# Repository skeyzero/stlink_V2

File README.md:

# STLink V2  Designed with KiCAD

## 说明  
本工程为Kicad工程，里面提供改硬件对应固件。使用说明请往下看。    

## 使用说明:
1.通过别的下载器将固件烧录进去。烧录成功后插入电脑能检测到stlink设备。   
2.打开stm32 ST-Link Utility.选择 ST-Link -> Firmware update 刷路最新固件。(这里通过usb更新固件,并非通过别的下载器更新)。    
3.完毕。 

## 原理图

## 效果图   

## 友情广告
PCB设计推荐软件Kicad，功能强大，开源免费,免除律师函警告。       
QQ群:924407324

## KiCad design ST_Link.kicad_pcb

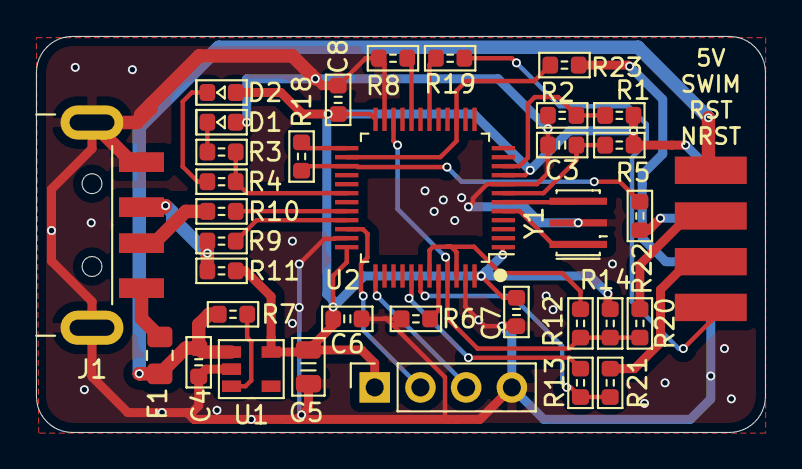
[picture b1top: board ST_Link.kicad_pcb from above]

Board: 2 copper layers, 40.5 x 22.0 mm, 36 parts (1 on the bottom side), 33 nets.

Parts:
C3: 22pF; 0603_C
C4: 1uF; 0603_C
C5: 10uF; 0805_C
C6, C7, C8: 100nF; 0603_C
D1: LED_B; 0603_LED
D2: LED_R; 0603_LED
F1: 0.5A; Fuse_0805_2012Metric_Pad1.15x1.40mm_HandSolder
J1: USB_A; USB_A_CNCTech_1001-011-01101_Horizontal
J2: Debug; PinSocket_1x04_P2.54mm_Vertical
J4: SWIM; cn_smt_2.54
J5: SWD; cn_smt_2.54
R1, R2: 4.7k; 0603_R
R3, R4, R11: 1k; 0603_R
R5, R6, R7, R8: 10k; 0603_R
R9, R10: 22R; 0603_R
R12, R13: 220R; 0603_R
R14: 680R; 0603_R
R18: 100R; 0603_R
R19, R20, R21, R22, R23: 20R; 0603_R
U1: ME6211C; SOT-23-5
U2: STM32F103_LQFP48; LQFP-48_7x7mm_P0.5mm
Y1: Crystal_CSTCE8M00; Resonator_SMD_muRata_CSTxExxV-3Pin_3.0x1.1mm_HandSoldering

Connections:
+3V3: C5.1, C6.1, C7.1, C8.1, D2.1, J2.1, J5.1, R1.1, R5.1, R11.1, R14.2, U1.5, U2.1, U2.9, U2.24, U2.36, U2.48
+5V: C4.1, F1.1, J4.1, R7.1, U1.1
/BOOT0: R6.1, U2.44
/BOOT1: R8.1, U2.20
/ISP_SWCLK: J2.3, U2.37
/ISP_SWDIO: J2.2, U2.34
/JTCK: R23.2, U2.15, U2.26
/JTMS: R18.1, R22.2, U2.27
/LED: R3.1, R4.1, U2.30
/NRST: R19.2, U2.18
/OSC_IN: U2.5, Y1.1
/OSC_OUT: U2.6, Y1.3
/PA0: R1.2, R2.1, U2.10
/RST: C3.1, R5.2, U2.7
/SWDIO_IN: R18.2, U2.25
/SWIM: R12.1, R14.1, R20.2, U2.22, U2.45
/SWIM_IN: R12.2, U2.43, U2.46
/SWIM_RST: R13.1, R21.2, U2.42
/SWIM_RST_IN: R13.2, U2.41
/USB_DM: J1.2, R10.1
/USB_DP: J1.3, R9.1, R11.2
GND: C3.2, C4.2, C5.2, C6.2, C7.2, C8.2, D1.1, J1.4, J1.5, J2.4, J5.4, R2.2, R6.2, R8.2, U1.2, U2.8, U2.23, U2.35, U2.47, Y1.2
unnamed: D1.2, R3.2
unnamed: D2.2, R4.2
unnamed: F1.2, J1.1
unnamed: J4.2, R20.1
unnamed: J4.3, R21.1
unnamed: J4.4, R19.1
unnamed: J5.2, R22.1
unnamed: J5.3, R23.1
unnamed: R7.2, U1.3
unnamed: R9.2, U2.33
unnamed: R10.2, U2.32

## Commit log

2019-11-25 stlink
